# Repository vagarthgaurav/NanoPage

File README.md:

# NanoPage

A custom e-reader board built around the Nordic nRF52840, in the form of an
Ebyte E73-2G4M08S1C module.

## Features

- Ebyte E73-2G4M08S1C module (Nordic nRF52840): Cortex-M4F, Bluetooth Low
  Energy, USB 2.0 full-speed
- E-paper (E Ink) panel via a 24-pin FPC connector, with its own onboard
  boost/negative-voltage generation (synchronous switcher, Schottky diode,
  inductor) to produce the panel's bias rails. It shares an SPI bus with
  the SD card, each with its own chip-select line.
- microSD card slot on the same SPI bus, power-gated by a load switch so
  it can be fully powered down between reads
- PCF85063ATL real-time clock on I2C with its own 32.768 kHz crystal and
  an interrupt line back to the MCU, for scheduling wake-ups while the MCU
  sleeps
- Power management: USB-C input for charging and USB data with ESD
  protection on the data lines, a linear Li-Po charger (BQ25170) and an
  impedance-track fuel gauge (MAX17055) sharing the I2C bus with the RTC,
  an automatic power-source mux between USB and battery, a pair of
  nanopower LDOs for the low-power rails, and a 2-pin JST battery
  connector
- Three tactile buttons (Action, Next, Prev), a dedicated reset button,
  and a 7-pin header for external or case-mounted buttons
- 3-pin JST-SH SWD connector (SWDIO / SWCLK / GND), wired to plug
  directly into a Raspberry Pi Debug Probe
- 6-layer PCB

See [docs/bootloader.md](docs/bootloader.md) for flashing the bootloader
over SWD.

## Pinout

Pin numbers below are the E73-2G4M08S1C module's physical pins (`U8` in
the schematic), not raw nRF52840 die pins.

| Module pin | nRF52840 GPIO | Function |
|---|---|---|
| 1  | P1.11        | SD card power enable |
| 2  | P1.10        | NC |
| 3  | P0.03/AIN1   | Charger status |
| 4  | P0.28/AIN4   | I2C SCL (RTC + fuel gauge) |
| 5  | GND          | Ground |
| 6  | P1.13        | I2C SDA (RTC + fuel gauge) |
| 7  | P0.02/AIN0   | RTC interrupt |
| 8  | P0.29/AIN5   | SPI MISO (display + SD card) |
| 9  | P0.31/AIN7   | SPI SCLK (display + SD card) |
| 10 | P0.30/AIN6   | SPI MOSI (display + SD card) |
| 11 | P0.00/XL1    | 32.768 kHz crystal |
| 12 | P0.26        | Display chip-select |
| 13 | P0.01/XL2    | 32.768 kHz crystal |
| 14 | P0.06        | Display data/command |
| 15 | P0.05/AIN3   | Display reset |
| 16 | P0.08        | Display busy |
| 17 | P1.09        | SD card chip-select |
| 18 | P0.04/AIN2   | NC |
| 19 | VDD          | +3.3V |
| 20 | P0.12        | SD card detect |
| 21 | GND          | Ground |
| 22 | P0.07        | NC |
| 23 | VDDH         | +3.3V |
| 24 | GND          | Ground |
| 25 | DCC          | DC/DC decoupling (internal) |
| 26 | P0.18/RESET  | Reset button |
| 27 | VBUS         | USB VBUS |
| 28 | P0.15        | NC |
| 29 | USB D-       | USB data |
| 30 | P0.17        | USB detect |
| 31 | USB D+       | USB data |
| 32 | P0.20        | NC |
| 33 | P0.13        | Fuel gauge alert |
| 34 | P0.22        | NC |
| 35 | P0.24        | Prev button |
| 36 | P1.00        | Charger power-good |
| 37 | SWDIO        | SWD data |
| 38 | P1.02        | NC |
| 39 | SWDCLK       | SWD clock |
| 40 | P1.04        | NC |
| 41 | P0.09/NFC1   | Action button |
| 42 | P1.06        | NC |
| 43 | P0.10/NFC2   | Next button |

P0.09 and P0.10 default to NFC antenna mode on the nRF52840. This board
has no NFC antenna, so firmware needs to switch those pins to GPIO mode
via UICR before the Action and Next buttons will read correctly (see
[docs/bootloader.md](docs/bootloader.md) for how this was done for the
bootloader).

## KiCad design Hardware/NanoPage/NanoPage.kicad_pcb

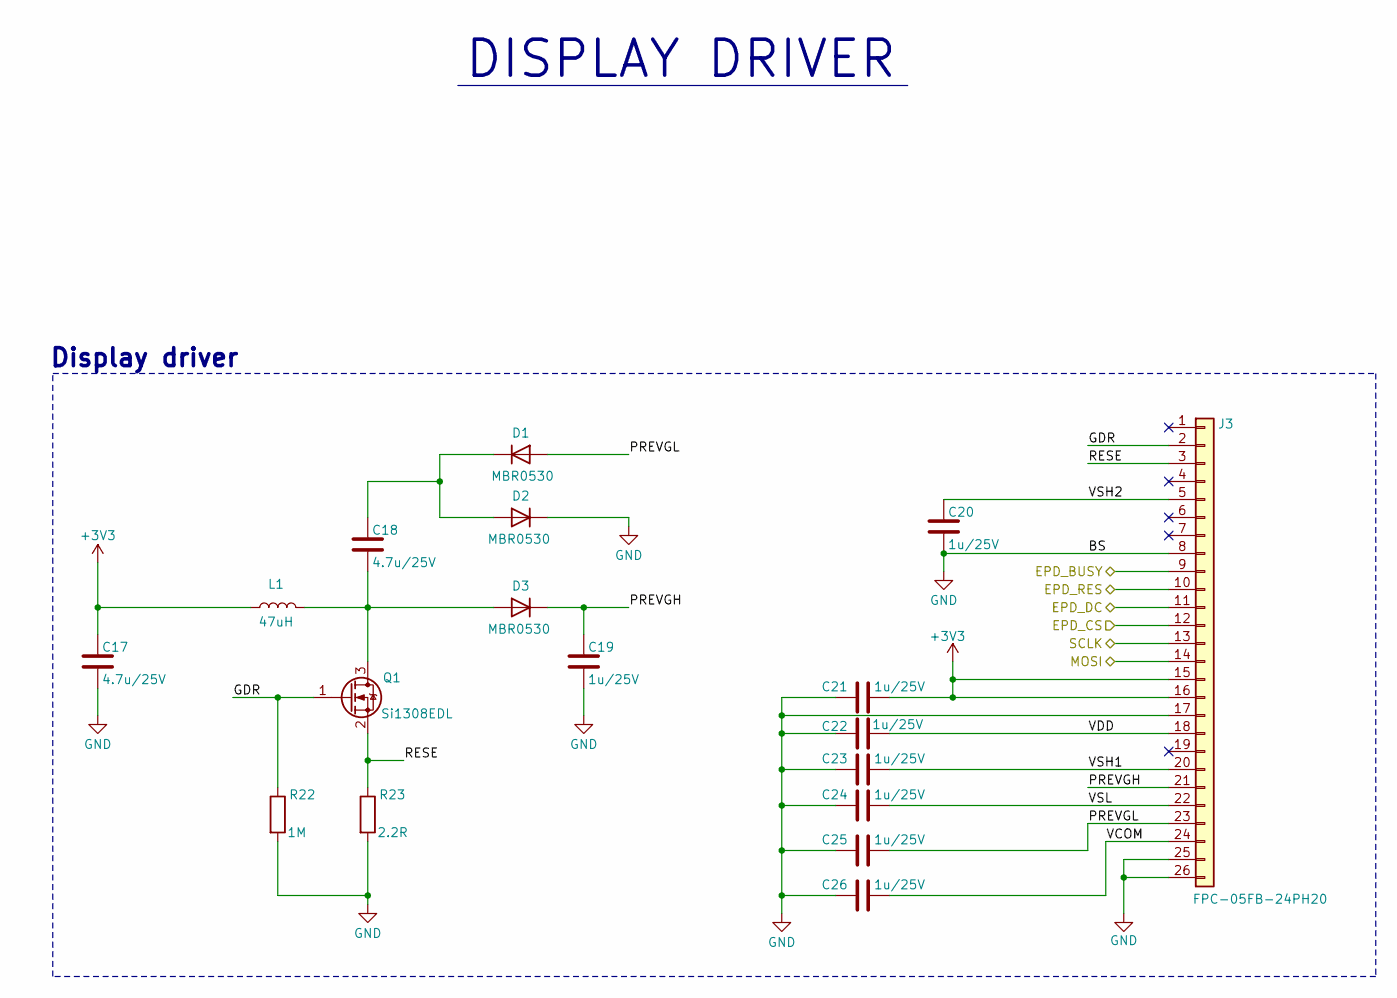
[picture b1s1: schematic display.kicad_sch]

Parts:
C17, C18: 4.7u/25V; C_0603_1608Metric
C19, C20, C21, C22, C23, C24, C25, C26: 1u/25V; C_0603_1608Metric
D1, D2, D3: MBR0530; D_SOD-123
J3: FPC-05FB-24PH20; XUNPU FPC-05FB-24PH20
L1: 47uH; NR4018
Q1: Si1308EDL; SOT-323_SC-70
R22: 1M; R_0603_1608Metric
R23: 2.2R; R_0603_1608Metric

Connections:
+3V3: C17.1, C21.2, J3.15, J3.16, L1.1; also elsewhere on the board
/Display/EPD_BUSY: J3.9; also elsewhere on the board
/Display/EPD_CS: J3.12; also elsewhere on the board
/Display/EPD_DC: J3.11; also elsewhere on the board
/Display/EPD_RES: J3.10; also elsewhere on the board
/Display/GDR: J3.2, Q1.1 (G), R22.1
/Display/MOSI: J3.14; also elsewhere on the board
/Display/PREVGH: C19.1, D3.1 (K), J3.21
/Display/PREVGL: C25.2, D1.2 (A), J3.23
/Display/RESE: J3.3, Q1.2 (S), R23.1
/Display/SCLK: J3.13; also elsewhere on the board
/Display/VCOM: C26.2, J3.24
/Display/VDD: C22.2, J3.18
/Display/VSH1: C23.2, J3.20
/Display/VSH2: C20.1, J3.5
/Display/VSL: C24.2, J3.22
GND: C17.2, C19.2, C20.2, C21.1, C22.1, C23.1, C24.1, C25.1, C26.1, D2.1 (K), J3.8, J3.17, J3.25, J3.26, R22.2, R23.2; also elsewhere on the board
unnamed: C18.1, D1.1 (K), D2.2 (A)
unnamed: C18.2, D3.2 (A), L1.2, Q1.3 (D)

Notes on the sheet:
Display driver
DISPLAY DRIVER

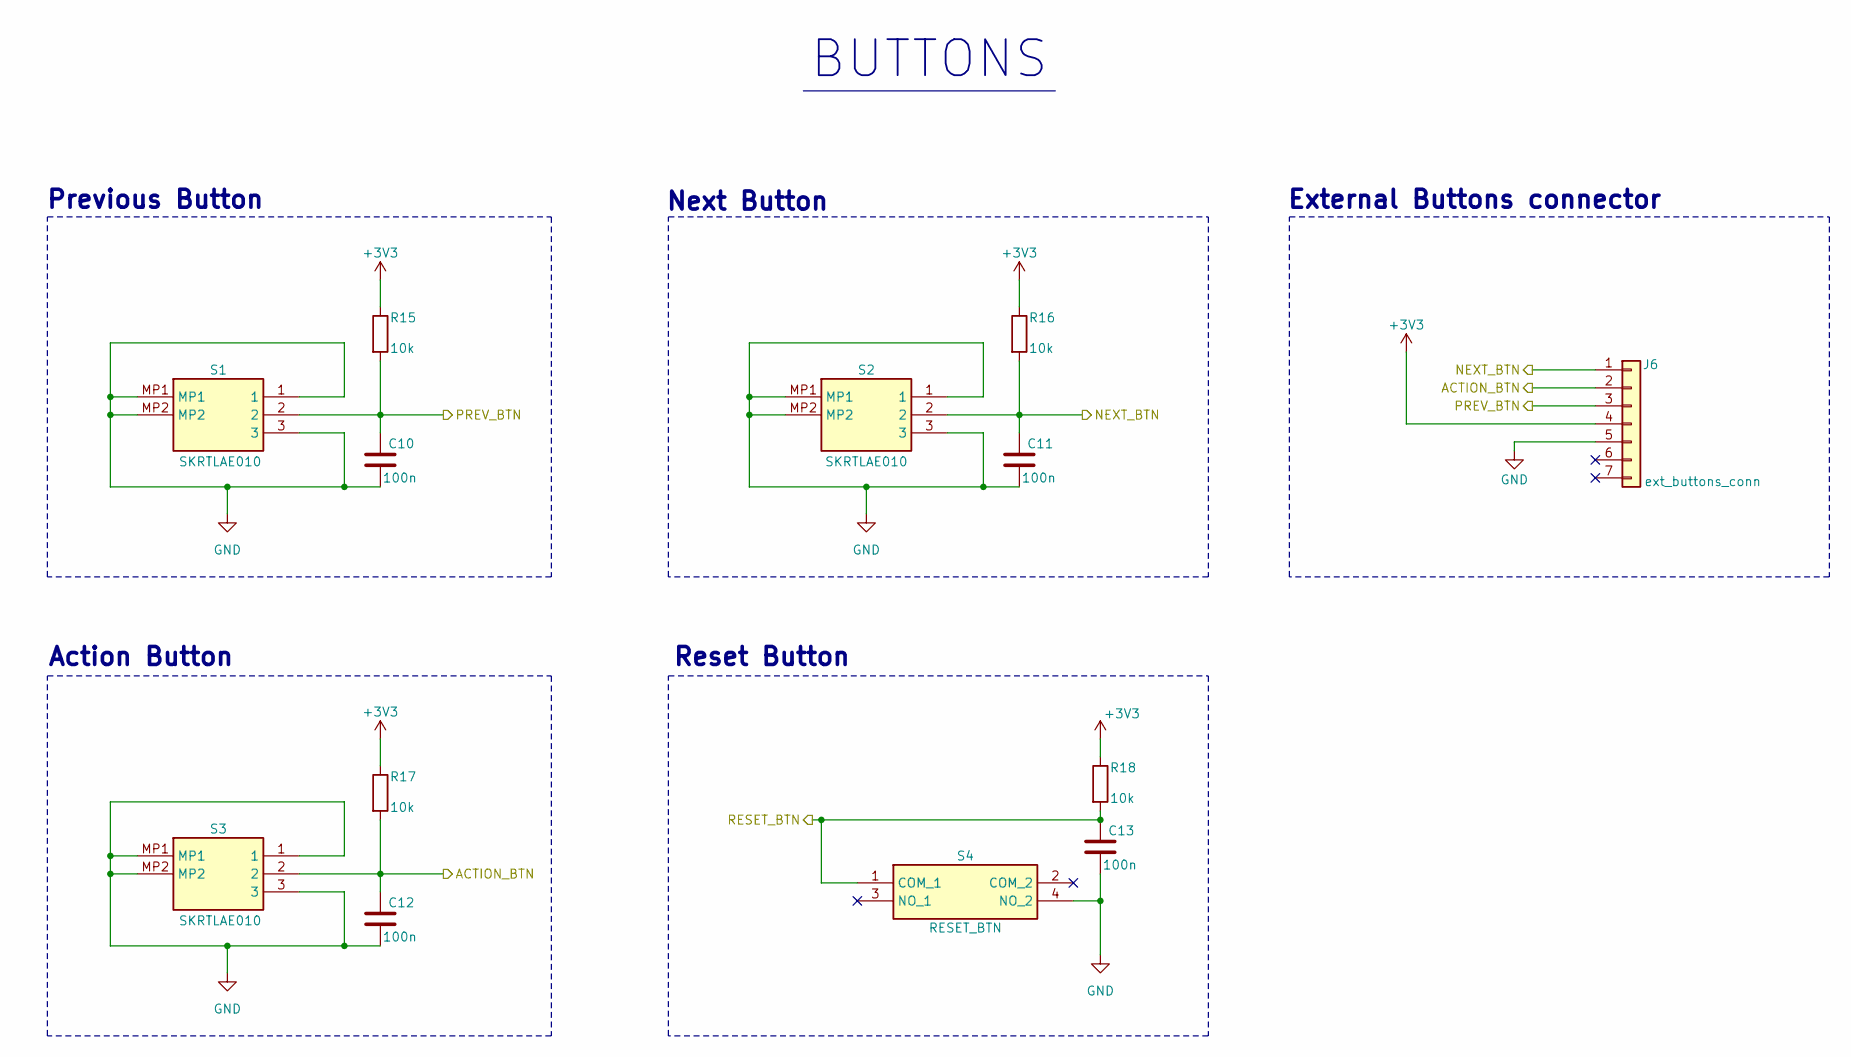
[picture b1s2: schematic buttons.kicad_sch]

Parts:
C10, C11, C12, C13: 100n; C_0402_1005Metric
J6: ext_buttons_conn; HC-FPC-05-09-5RLTAG
R15, R16, R17, R18: 10k; R_0402_1005Metric
S1, S2, S3: SKRTLAE010; Mouser Part Number 688-SKRTLA
S4: RESET_BTN; PTS526SM15SMTR2LFS; Mouser Part Number 611-PTS526SM15SMTR2L

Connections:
+3V3: J6.4, R15.1, R16.1, R17.1, R18.1; also elsewhere on the board
/Buttons/ACTION_BTN: C12.1, J6.2, R17.2, S3.2; also elsewhere on the board
/Buttons/NEXT_BTN: C11.1, J6.1, R16.2, S2.2; also elsewhere on the board
/Buttons/PREV_BTN: C10.1, J6.3, R15.2, S1.2; also elsewhere on the board
/Buttons/RESET_BTN: C13.1, R18.2, S4.1 (COM_1); also elsewhere on the board
GND: C10.2, C11.2, C12.2, C13.2, J6.5, S1.1, S1.3, S1.MP1, S1.MP2, S2.1, S2.3, S2.MP1, S2.MP2, S3.1, S3.3, S3.MP1, S3.MP2, S4.4 (NO_2); also elsewhere on the board

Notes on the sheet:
External Buttons connector
Reset Button
Action Button
BUTTONS
Next Button
Previous Button

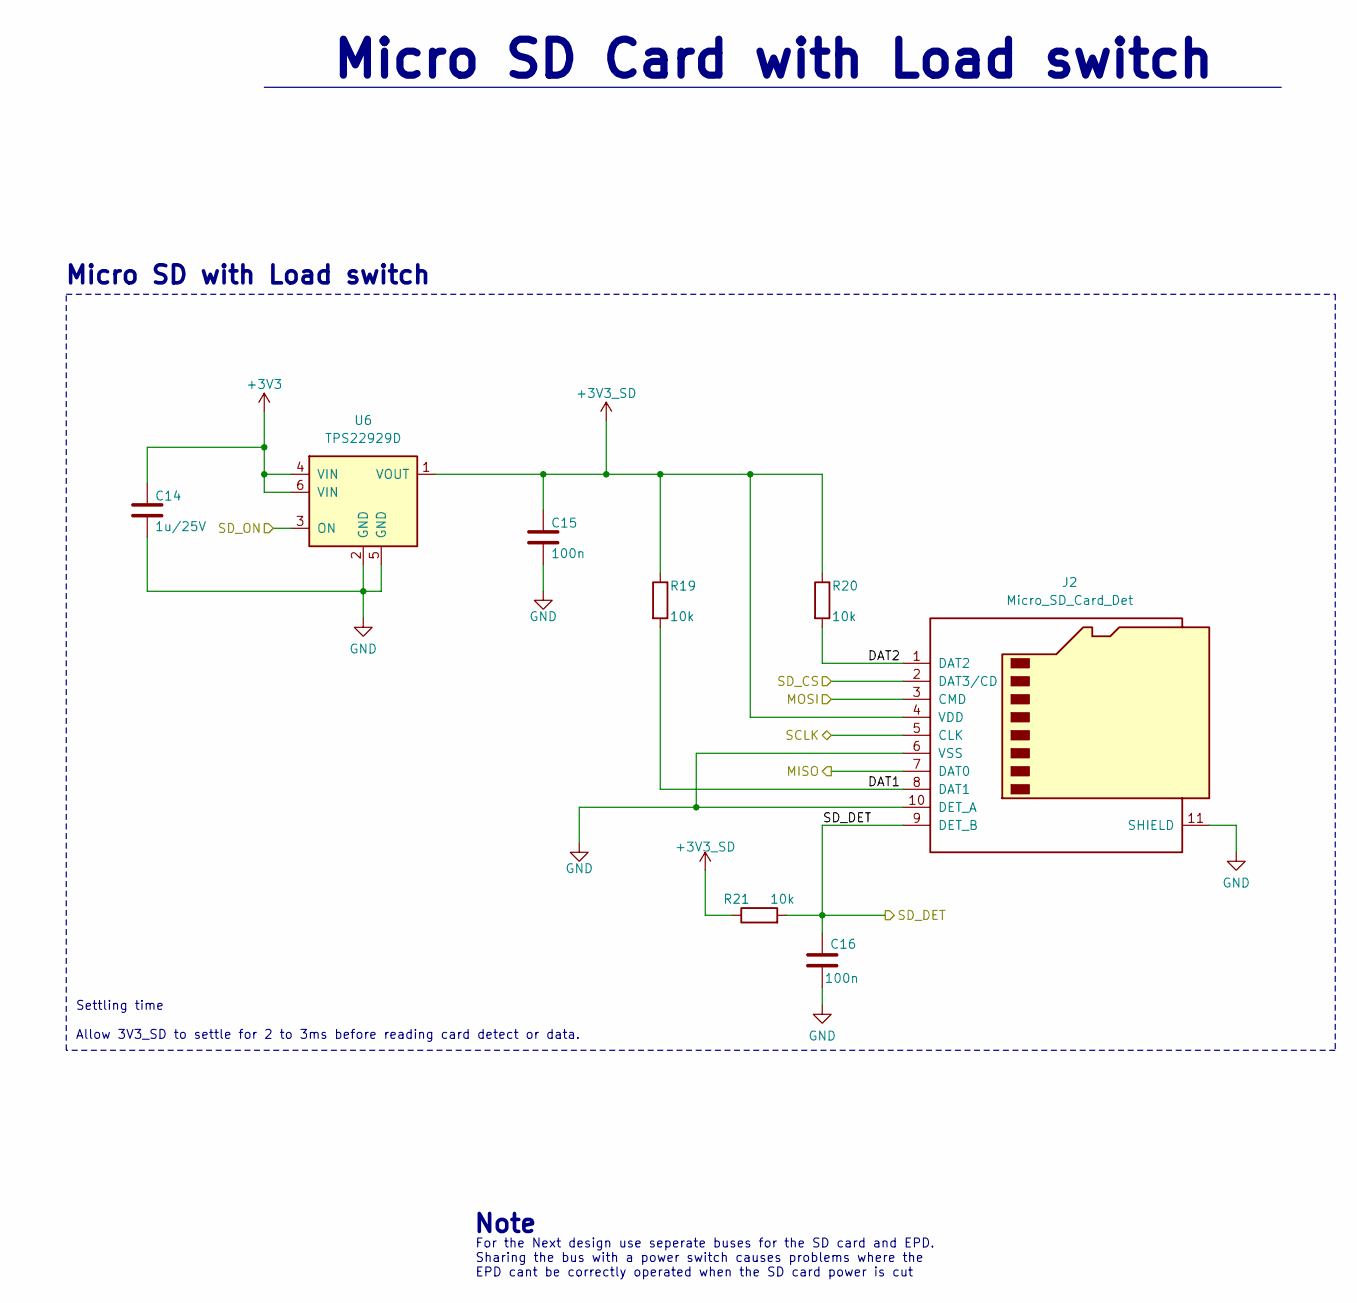
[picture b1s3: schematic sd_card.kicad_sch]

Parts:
C14: 1u/25V; C_0603_1608Metric
C15, C16: 100n; C_0402_1005Metric
J2: Micro_SD_Card_Det; microSD_HC_Molex_104031-0811
R19, R20, R21: 10k; R_0402_1005Metric
U6: TPS22929D; SOT-23-6

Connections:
+3V3: C14.1, U6.4 (VIN), U6.6 (VIN); also elsewhere on the board
+3V3_SD: C15.1, J2.4 (VDD), R19.1, R20.1, R21.1, U6.1 (VOUT)
/Display/MOSI: J2.3 (CMD); also elsewhere on the board
/Display/SCLK: J2.5 (CLK); also elsewhere on the board
/Microcontroller/MCU_SD_CS: J2.2 (DAT3/CD); also elsewhere on the board
/Microcontroller/MCU_SD_ON: U6.3 (ON); also elsewhere on the board
/Microcontroller/MISO: J2.7 (DAT0); also elsewhere on the board
/SD Card/DAT1: J2.8 (DAT1), R19.2
/SD Card/DAT2: J2.1 (DAT2), R20.2
/SD Card/SD_DET: C16.1, J2.9 (DET_B), R21.2; also elsewhere on the board
GND: C14.2, C15.2, C16.2, J2.6 (VSS), J2.10 (DET_A), J2.11 (SHIELD), U6.2 (GND), U6.5 (GND); also elsewhere on the board

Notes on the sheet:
Settling time Allow 3V3_SD to settle for 2 to 3ms before reading card detect or data.
For the Next design use seperate buses for the SD card and EPD. Sharing the bus with a power switch causes problems where the EPD cant be correctly operated when the SD card power is cut
Micro SD Card with Load switch
Note
Micro SD with Load switch

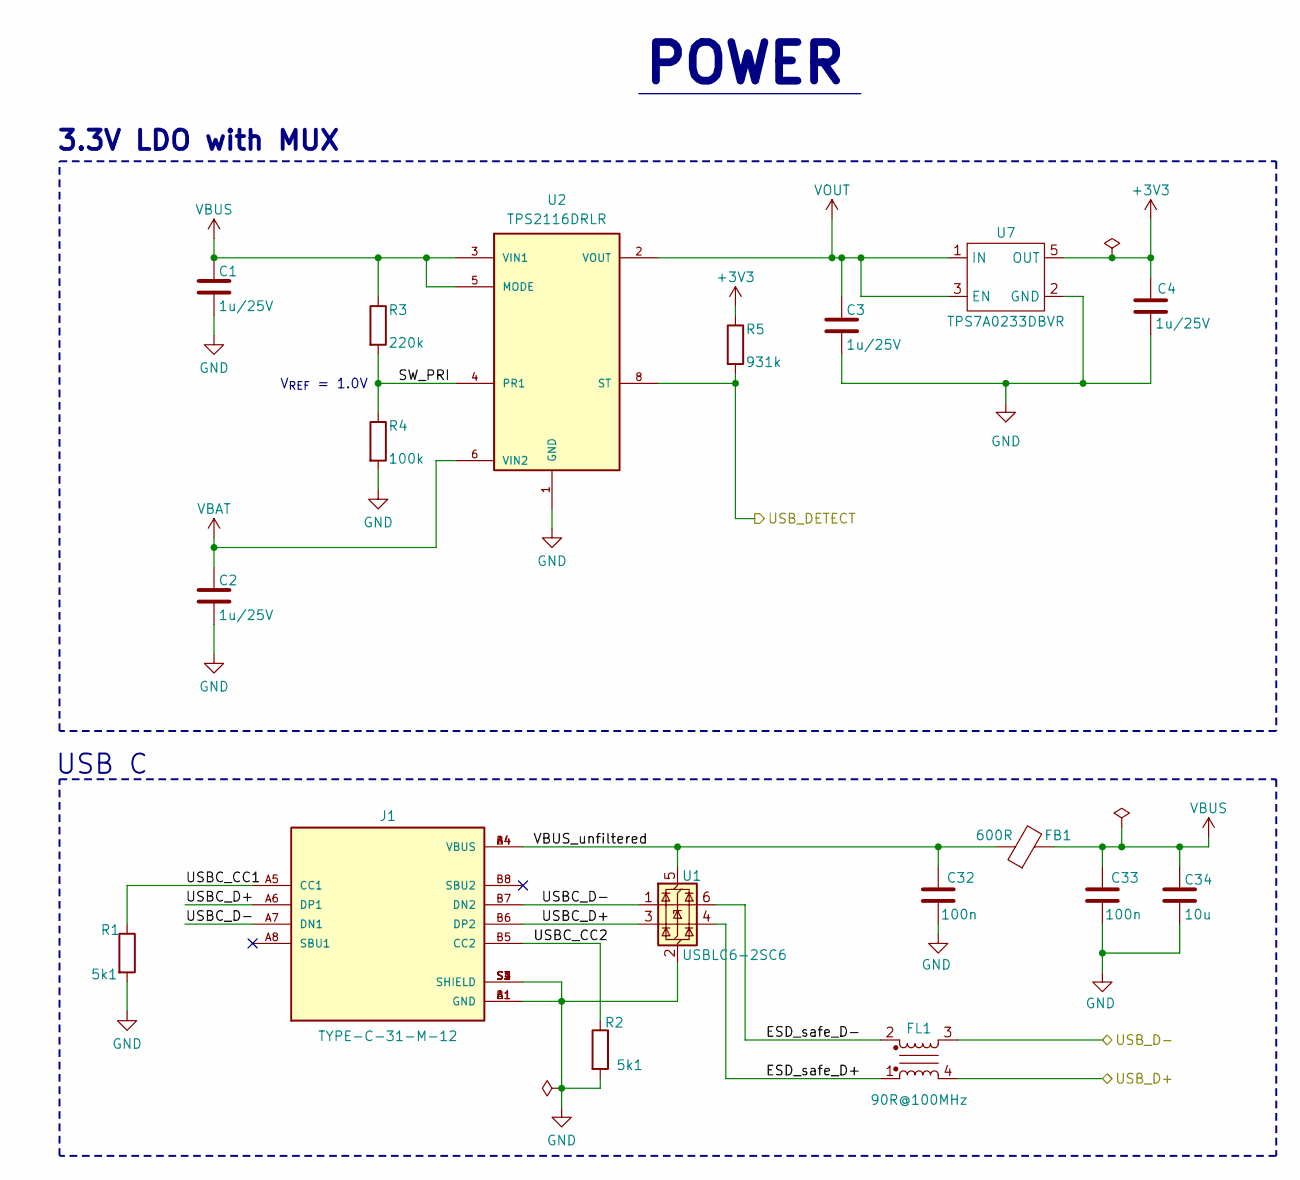
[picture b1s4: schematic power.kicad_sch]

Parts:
C1, C2, C3, C4: 1u/25V; C_0603_1608Metric
C32, C33: 100n; C_0402_1005Metric
C34: 10u; C_0603_1608Metric
FB1: 600R; L_0603_1608Metric
FL1: 90R@100MHz; L_CommonModeChoke_TDK_0503USB
J1: TYPE-C-31-M-12; HRO_TYPE-C-31-M-12; PARTREV 2020.12.08
R1, R2: 5k1; R_0402_1005Metric
R3: 220k; R_0402_1005Metric
R4: 100k; R_0402_1005Metric
R5: 931k; R_0402_1005Metric
U1: USBLC6-2SC6; SOT-23-6
U2: TPS2116DRLR; SOTFL50P160X60-8N; PARTREV A
U7: TPS7A0233DBVR; SOT-23-5

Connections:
+3V3: C4.1, R5.1, U7.5 (OUT); also elsewhere on the board
/Microcontroller/MCU_USB_D+: FL1.4; also elsewhere on the board
/Microcontroller/MCU_USB_D-: FL1.3; also elsewhere on the board
/Microcontroller/MCU_USB_DETECT: R5.2, U2.8 (ST); also elsewhere on the board
/Power/ESD_safe_D+: FL1.1, U1.4 (I/O2)
/Power/ESD_safe_D-: FL1.2, U1.6 (I/O1)
/Power/SW_PRI: R3.2, R4.1, U2.4 (PR1)
/Power/USBC_CC1: J1.A5 (CC1), R1.1
/Power/USBC_CC2: J1.B5 (CC2), R2.1
/Power/USBC_D+: J1.A6 (DP1), J1.B6 (DP2), U1.3 (I/O2)
/Power/USBC_D-: J1.A7 (DN1), J1.B7 (DN2), U1.1 (I/O1)
/Power/VBUS_unfiltered: C32.1, FB1.1, J1.A4 (VBUS), J1.B4 (VBUS), U1.5 (VBUS)
GND: C1.2, C2.2, C3.2, C4.2, C32.2, C33.2, C34.2, J1.A1 (GND), J1.B1 (GND), J1.S1 (SHIELD), J1.S2 (SHIELD), J1.S3 (SHIELD), J1.S4 (SHIELD), R1.2, R2.2, R4.2, U1.2 (GND), U2.1 (GND), U7.2 (GND); also elsewhere on the board
VBAT: C2.1, U2.6 (VIN2); also elsewhere on the board
VBUS: C1.1, C33.1, C34.1, FB1.2, R3.1, U2.3 (VIN1), U2.5 (MODE); also elsewhere on the board
VOUT: C3.1, U2.2 (VOUT), U2.7 (VOUT), U7.1 (IN), U7.3 (EN)

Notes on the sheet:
POWER
3.3V LDO with MUX
V_{REF} = 1.0V
USB C

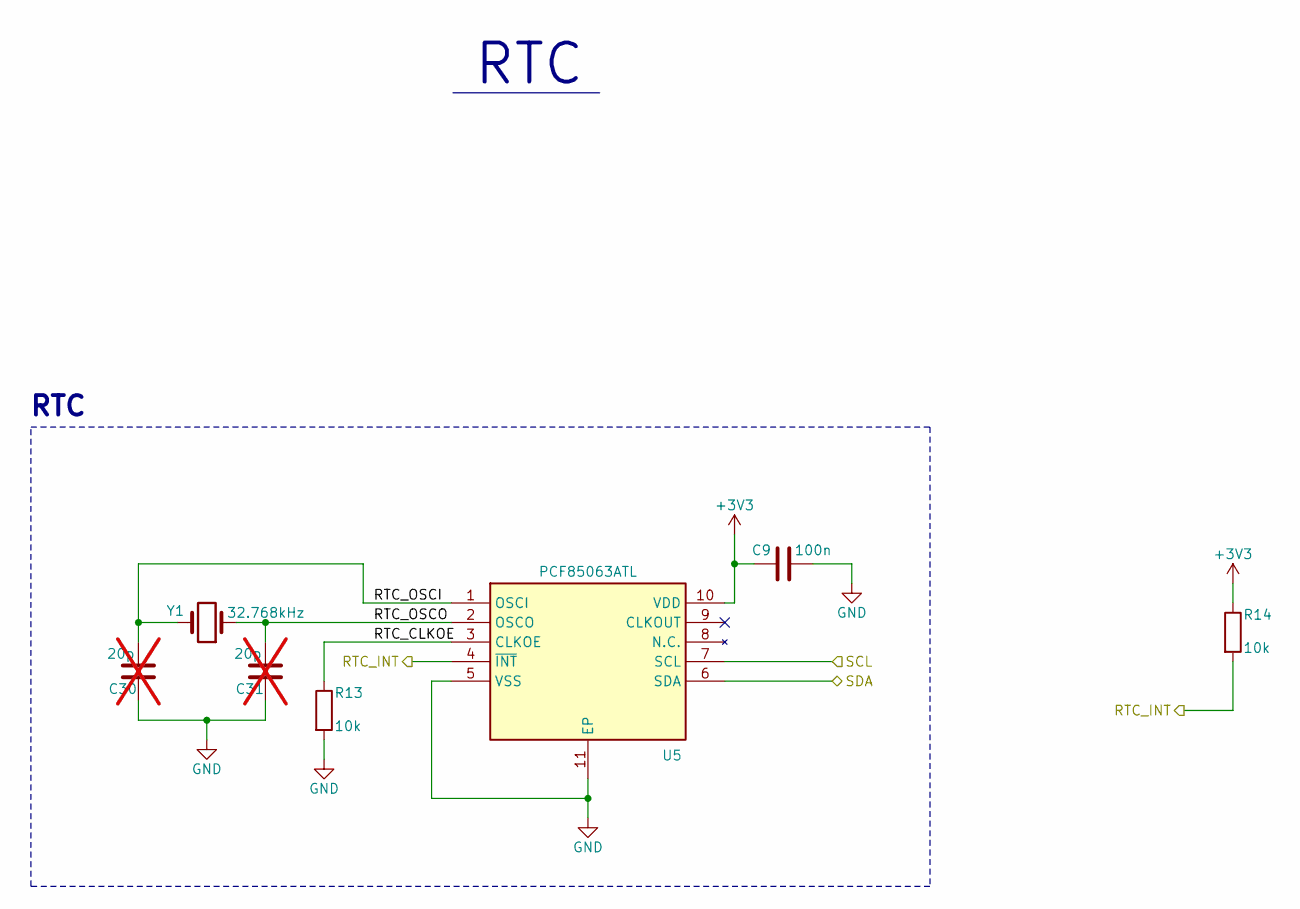
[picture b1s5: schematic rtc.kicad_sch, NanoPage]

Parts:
C9: 100n; C_0402_1005Metric
C30, C31: 20p; C_0402_1005Metric; not fitted
R13, R14: 10k; R_0402_1005Metric
U5: PCF85063ATL; SON50P260X260X50-11N; Mouser Part Number 771-PCF85063ATL1118
Y1: 32.768kHz; Crystal_SMD_3215-2Pin_3.2x1.5mm

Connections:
+3V3: C9.1, R14.1, U5.10 (VDD); also elsewhere on the board
/Battery Charger and Fuel Gauge/SCL: U5.7 (SCL); also elsewhere on the board
/Battery Charger and Fuel Gauge/SDA: U5.6 (SDA); also elsewhere on the board
/Microcontroller/MCU_RTC_INT: R14.2, U5.4 (~INT); also elsewhere on the board
/RTC/RTC_CLKOE: R13.1, U5.3 (CLKOE)
/RTC/RTC_OSCI: C30.2, U5.1 (OSCI), Y1.2
/RTC/RTC_OSCO: C31.2, U5.2 (OSCO), Y1.1
GND: C9.2, C30.1, C31.1, R13.2, U5.5 (VSS), U5.11 (EP); also elsewhere on the board

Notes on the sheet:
RTC

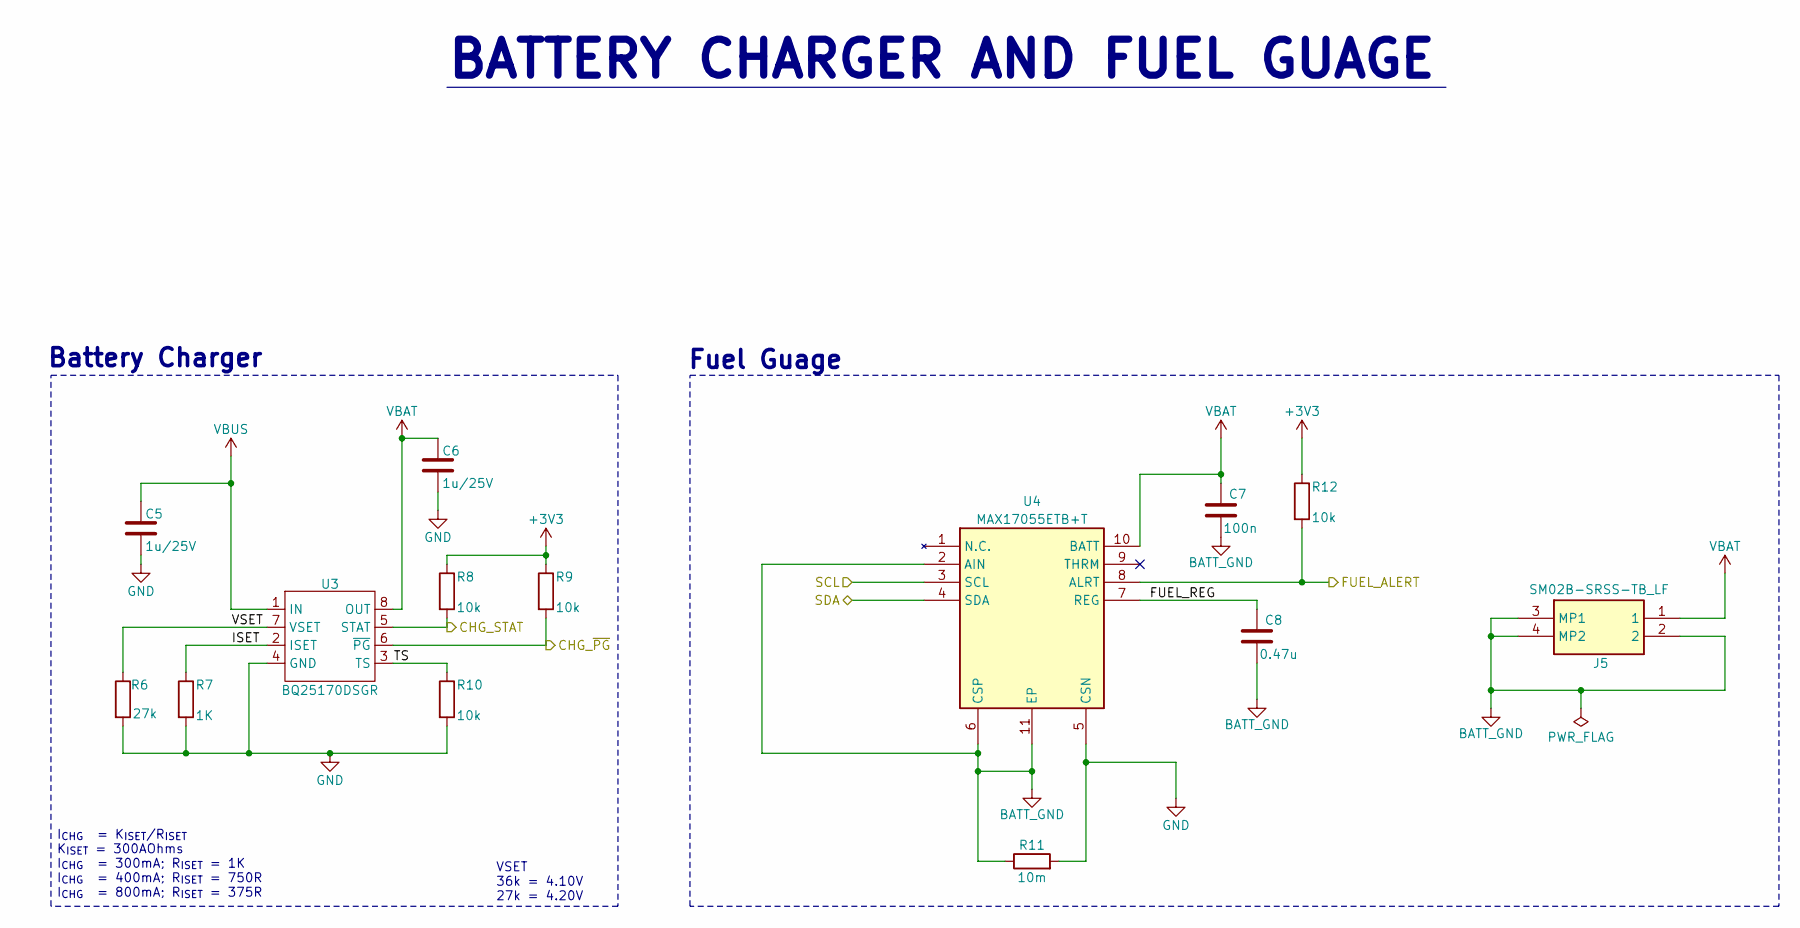
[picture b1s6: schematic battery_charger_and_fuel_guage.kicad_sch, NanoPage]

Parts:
C5, C6: 1u/25V; C_0603_1608Metric
C7: 100n; C_0402_1005Metric
C8: 0.47u; C_0402_1005Metric
J5: SM02B-SRSS-TB_LF; SM02BSRSSTBLFSN; Mouser Part Number N/A
R6: 27k; R_0402_1005Metric
R7: 1K; R_0402_1005Metric
R8, R9, R10, R12: 10k; R_0402_1005Metric
R11: 10m; R_0805_2012Metric
U3: BQ25170DSGR; BQ25170
U4: MAX17055ETB+T; SON40P250X200X80-11N; Mouser Part Number 700-MAX17055ETB+T

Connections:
+3V3: R8.1, R9.1, R12.1; also elsewhere on the board
/Battery Charger and Fuel Gauge/CHG_STAT: R8.2, U3.5 (STAT); also elsewhere on the board
/Battery Charger and Fuel Gauge/CHG_~PG: R9.2, U3.6 (~PG); also elsewhere on the board
/Battery Charger and Fuel Gauge/FUEL_ALERT: R12.2, U4.8 (ALRT); also elsewhere on the board
/Battery Charger and Fuel Gauge/FUEL_REG: C8.1, U4.7 (REG)
/Battery Charger and Fuel Gauge/ISET: R7.1, U3.2 (ISET)
/Battery Charger and Fuel Gauge/SCL: U4.3 (SCL); also elsewhere on the board
/Battery Charger and Fuel Gauge/SDA: U4.4 (SDA); also elsewhere on the board
/Battery Charger and Fuel Gauge/TS: R10.1, U3.3 (TS)
/Battery Charger and Fuel Gauge/VSET: R6.1, U3.7 (VSET)
BATT_GND: C7.2, C8.2, J5.2, J5.3 (MP1), J5.4 (MP2), R11.1, U4.2 (AIN), U4.6 (CSP), U4.11 (EP)
GND: C5.2, C6.2, R6.2, R7.2, R10.2, R11.2, U3.4 (GND), U3.9 (PAD), U4.5 (CSN); also elsewhere on the board
VBAT: C6.1, C7.1, J5.1, U3.8 (OUT), U4.10 (BATT); also elsewhere on the board
VBUS: C5.1, U3.1 (IN); also elsewhere on the board

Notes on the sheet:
Fuel Guage
I_{CHG} = K_{ISET}/R_{ISET} K_{ISET} = 300AOhms I_{CHG} = 300mA; R_{ISET} = 1K I_{CHG} = 400mA; R_{ISET} = 750R I_{CHG} = 800mA; R_{ISET} = 375R
Battery Charger
BATTERY CHARGER AND FUEL GUAGE
VSET 36k = 4.10V 27k = 4.20V

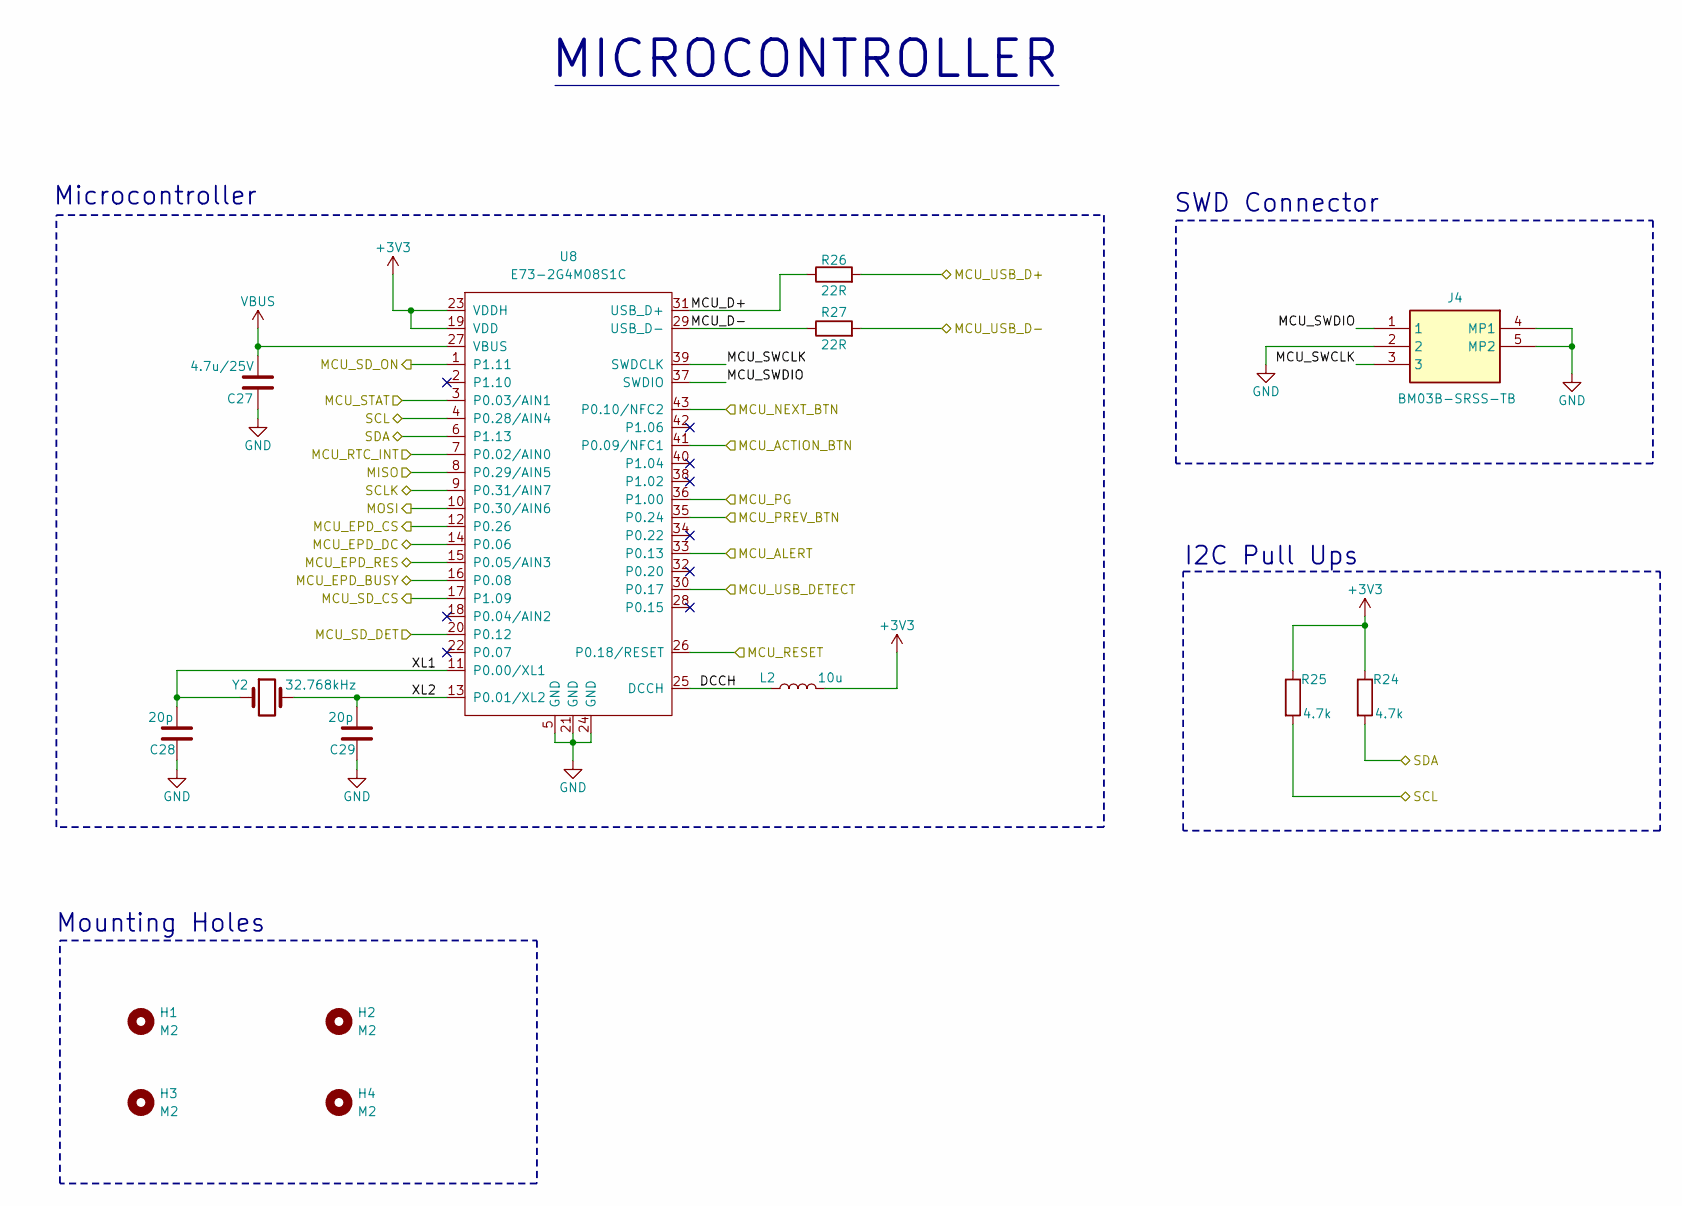
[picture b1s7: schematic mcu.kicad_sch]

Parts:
C27: 4.7u/25V; C_0603_1608Metric
C28, C29: 20p; C_0402_1005Metric
H1, H2, H3, H4: M2; MountingHole_2.2mm_M2_DIN965
J4: BM03B-SRSS-TB; BM03BSRSSTBLFSN; Mouser Part Number 306-BM03BSRSSTBLFSNP
L2: 10u; L_0603_1608Metric
R24, R25: 4.7k; R_0402_1005Metric
R26, R27: 22R; R_0402_1005Metric
U8: E73-2G4M08S1C
Y2: 32.768kHz; Crystal_SMD_3215-2Pin_3.2x1.5mm

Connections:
+3V3: L2.2, R24.1, R25.1, U8.19 (VDD), U8.23 (VDDH); also elsewhere on the board
/Battery Charger and Fuel Gauge/CHG_STAT: U8.3 (P0.03/AIN1); also elsewhere on the board
/Battery Charger and Fuel Gauge/CHG_~PG: U8.36 (P1.00); also elsewhere on the board
/Battery Charger and Fuel Gauge/FUEL_ALERT: U8.33 (P0.13); also elsewhere on the board
/Battery Charger and Fuel Gauge/SCL: R25.2, U8.4 (P0.28/AIN4); also elsewhere on the board
/Battery Charger and Fuel Gauge/SDA: R24.2, U8.6 (P1.13); also elsewhere on the board
/Buttons/ACTION_BTN: U8.41 (P0.09/NFC1); also elsewhere on the board
/Buttons/NEXT_BTN: U8.43 (P0.10/NFC2); also elsewhere on the board
/Buttons/PREV_BTN: U8.35 (P0.24); also elsewhere on the board
/Buttons/RESET_BTN: U8.26 (P0.18/RESET); also elsewhere on the board
/Display/EPD_BUSY: U8.16 (P0.08); also elsewhere on the board
/Display/EPD_CS: U8.12 (P0.26); also elsewhere on the board
/Display/EPD_DC: U8.14 (P0.06); also elsewhere on the board
/Display/EPD_RES: U8.15 (P0.05/AIN3); also elsewhere on the board
/Display/MOSI: U8.10 (P0.30/AIN6); also elsewhere on the board
/Display/SCLK: U8.9 (P0.31/AIN7); also elsewhere on the board
/Microcontroller/DCCH: L2.1, U8.25 (DCCH)
/Microcontroller/MCU_D+: R26.1, U8.31 (USB_D+)
/Microcontroller/MCU_D-: R27.1, U8.29 (USB_D-)
/Microcontroller/MCU_RTC_INT: U8.7 (P0.02/AIN0); also elsewhere on the board
/Microcontroller/MCU_SD_CS: U8.17 (P1.09); also elsewhere on the board
/Microcontroller/MCU_SD_ON: U8.1 (P1.11); also elsewhere on the board
/Microcontroller/MCU_SWCLK: J4.3, U8.39 (SWDCLK)
/Microcontroller/MCU_SWDIO: J4.1, U8.37 (SWDIO)
/Microcontroller/MCU_USB_D+: R26.2; also elsewhere on the board
/Microcontroller/MCU_USB_D-: R27.2; also elsewhere on the board
/Microcontroller/MCU_USB_DETECT: U8.30 (P0.17); also elsewhere on the board
/Microcontroller/MISO: U8.8 (P0.29/AIN5); also elsewhere on the board
/Microcontroller/XL1: C28.2, U8.11 (P0.00/XL1), Y2.1
/Microcontroller/XL2: C29.2, U8.13 (P0.01/XL2), Y2.2
/SD Card/SD_DET: U8.20 (P0.12); also elsewhere on the board
GND: C27.1, C28.1, C29.1, J4.2, J4.4 (MP1), J4.5 (MP2), U8.5 (GND), U8.21 (GND), U8.24 (GND); also elsewhere on the board
VBUS: C27.2, U8.27 (VBUS); also elsewhere on the board

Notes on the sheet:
Microcontroller
SWD Connector
Mounting Holes
MICROCONTROLLER
I2C Pull Ups

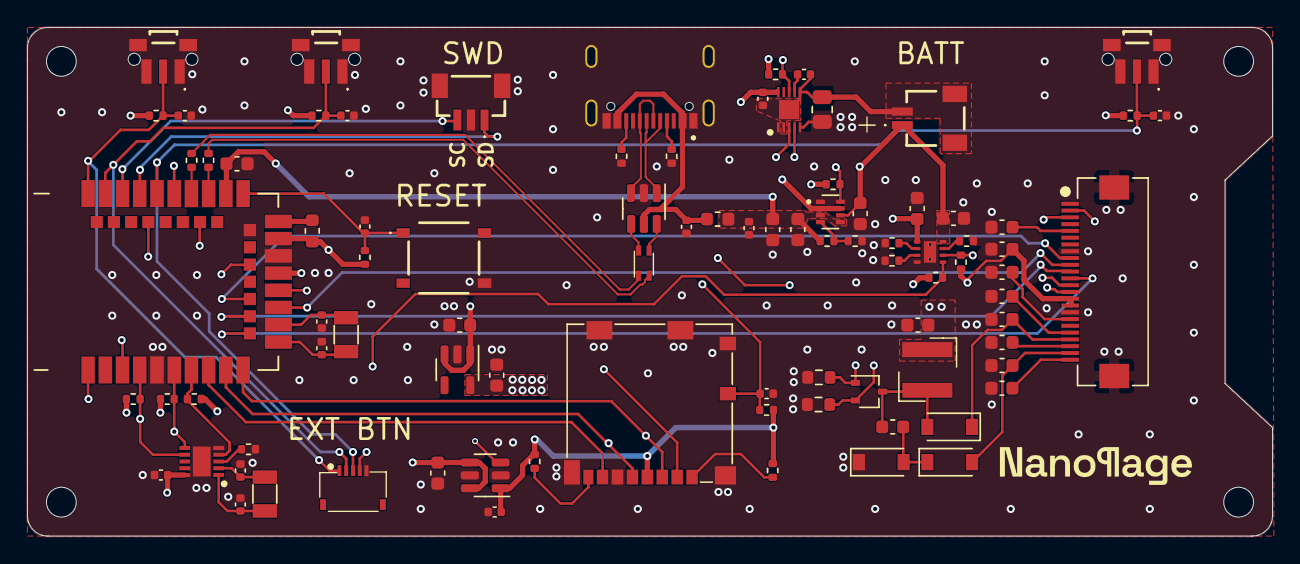
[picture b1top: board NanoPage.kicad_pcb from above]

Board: 6 copper layers, 91.8 x 37.5 mm, 93 parts (0 on the bottom side), 65 nets.

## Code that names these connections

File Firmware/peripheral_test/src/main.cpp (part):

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// Full-height single buffer (128x296/8 = 4736 bytes) - plenty of RAM on
// the nRF52840, no need for GxEPD2's paged/partial-buffer drawing.
GxEPD2_BW<GxEPD2_290_GDEY029T94, GxEPD2_290_GDEY029T94::HEIGHT> display(
    GxEPD2_290_GDEY029T94(PIN_EPD_CS, PIN_EPD_DC, PIN_EPD_RST, PIN_EPD_BUSY));

// ---- microSD card -------------------------------------------------------
SdFat sd;
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    {PIN_BTN_ACTION, "ACTION button", true, false},
    {PIN_BTN_NEXT, "NEXT button", true, false},
    {PIN_RTC_INT, "RTC ~INT", true, false},
    {PIN_FUEL_ALERT, "Fuel gauge ALRT", true, false},
    {PIN_USB_DETECT, "USB detect (power mux ST)", false, false},
};
static const size_t NUM_INPUTS = sizeof(inputs) / sizeof(inputs[0]);
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  bool fuelOk = max17055ReadReg(FUEL_REG_VCELL, &vcellRaw) &&
                max17055ReadReg(FUEL_REG_REPSOC, &socRaw) &&
                max17055ReadReg(FUEL_REG_CURRENT, &currentRaw);
  bool powerGood = digitalRead(PIN_CHG_PG) == LOW;
  bool charging = digitalRead(PIN_CHG_STAT) == LOW;

  Serial.println(F("--- status ---"));
  printRtcStatus(rtcRegs, rtcOk);
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  // like the inputs[] pins above), so they need their own pinMode() - an
  // unconfigured nRF52840 pin's input buffer is disconnected by default,
  // which was making digitalRead() on these always come back LOW.
  pinMode(PIN_CHG_PG, INPUT_PULLUP);
  pinMode(PIN_CHG_STAT, INPUT_PULLUP);

  Wire.begin();
  Wire.setClock(100000);
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
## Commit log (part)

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2026-05-29 feat: Final board layout
2026-05-29 docs: Add additional dimensioning
